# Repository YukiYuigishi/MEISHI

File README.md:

# MEISHI
[2022 v1.0](https://github.com/YukiYuigishi/MEISHI/tree/master/PCB/MEISHI2022)

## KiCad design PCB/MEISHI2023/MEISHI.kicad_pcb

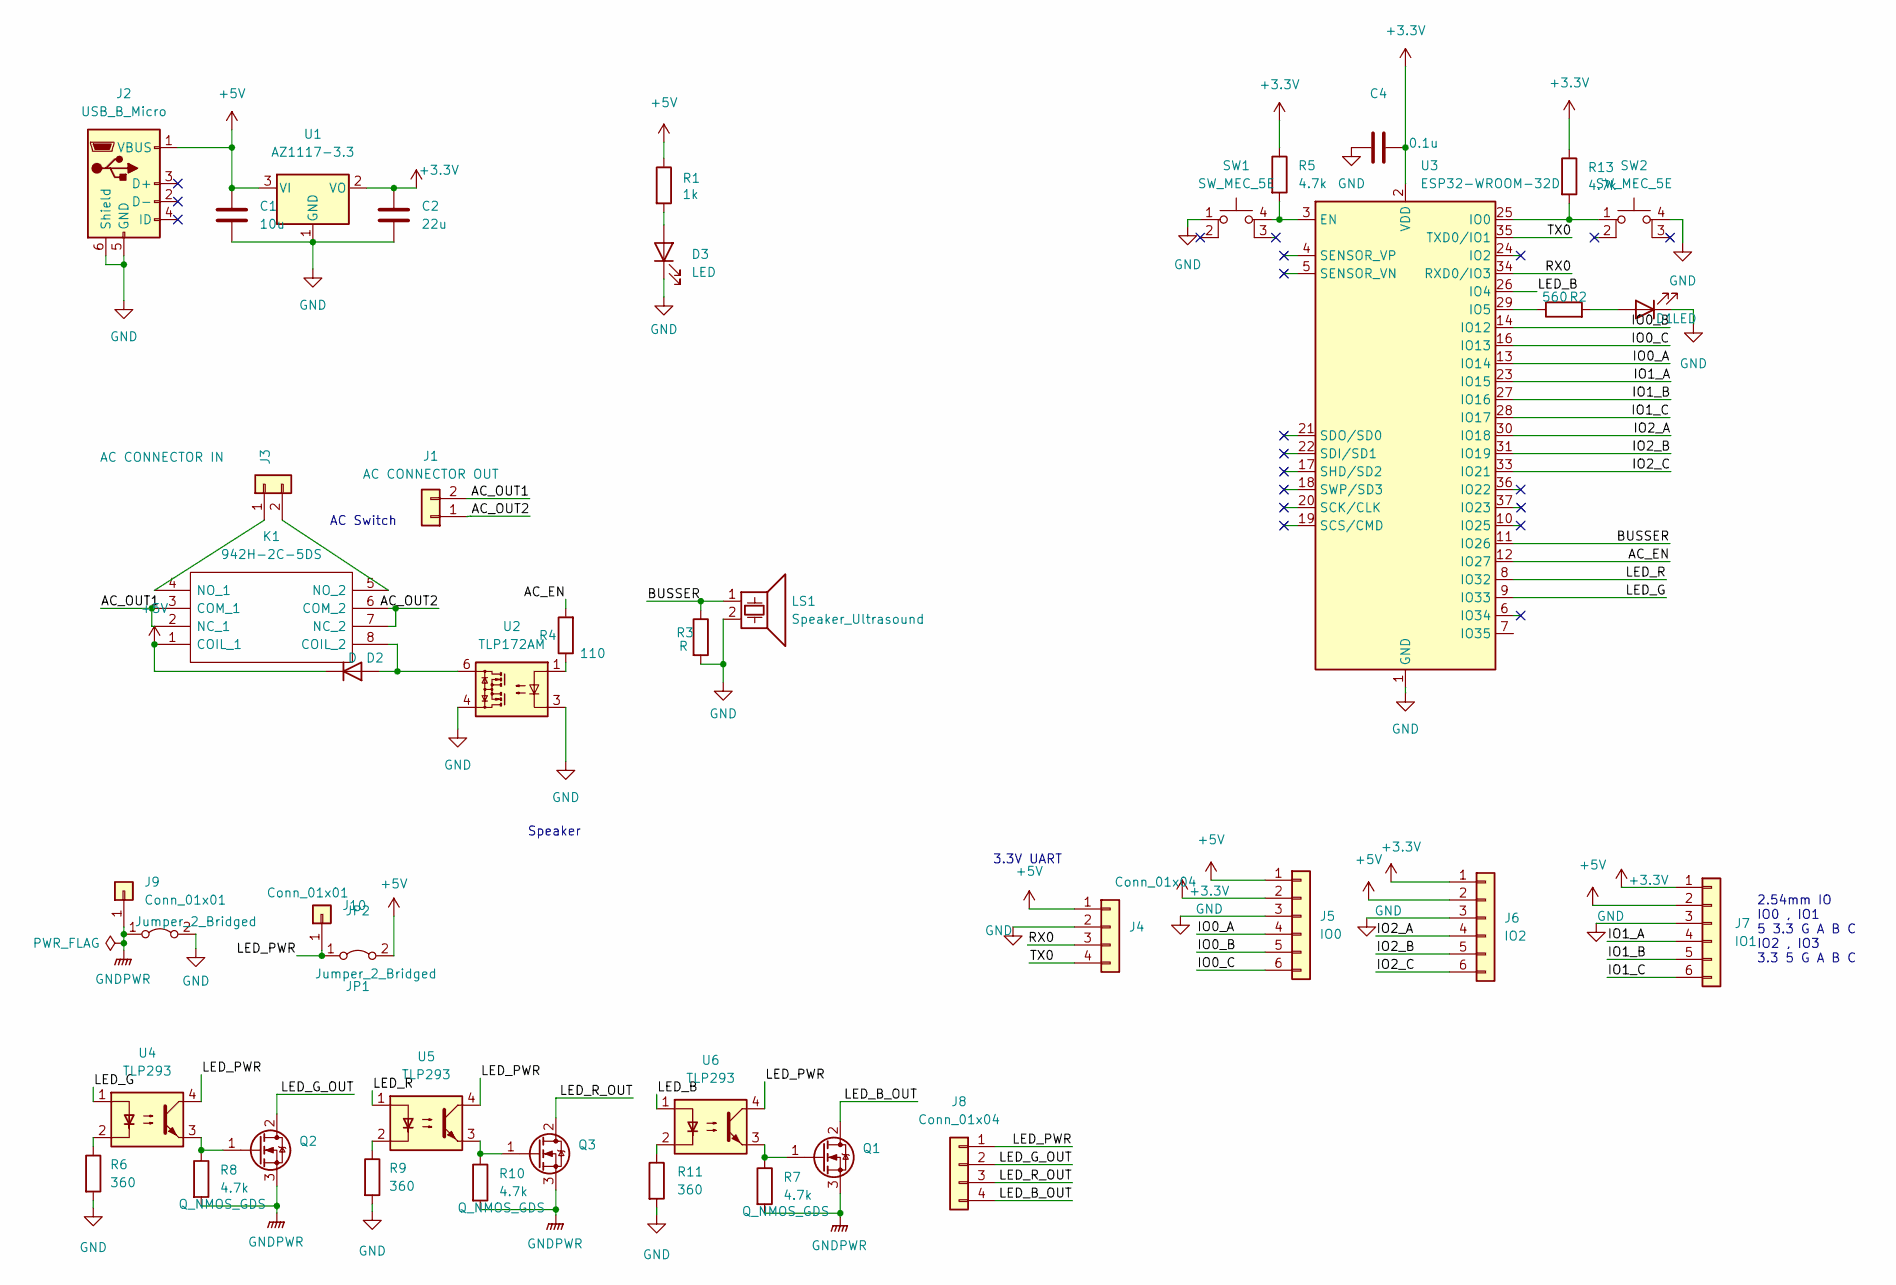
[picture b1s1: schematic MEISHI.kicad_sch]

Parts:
C1: 10u; C_0805_2012Metric_Pad1.18x1.45mm_HandSolder
C2: 22u; C_0805_2012Metric_Pad1.18x1.45mm_HandSolder
C4: 0.1u; C_0805_2012Metric_Pad1.18x1.45mm_HandSolder
D1, D3: LED; LED_0603_1608Metric_Pad1.05x0.95mm_HandSolder
D2: D; D_SOD-128
J1: AC CONNECTOR OUT; JST_VH_B2P-VH_1x02_P3.96mm_Vertical
J2: USB_B_Micro; Micro-USB-J91(Marutsu)
J3: AC CONNECTOR IN; JST_VH_B2P-VH_1x02_P3.96mm_Vertical
J4, J8: Conn_01x04; JST_XH_B4B-XH-A_1x04_P2.50mm_Vertical
J5: IO0; JST_XH_B6B-XH-A_1x06_P2.50mm_Vertical
J6: IO2; JST_XH_B6B-XH-A_1x06_P2.50mm_Vertical
J7: IO1; JST_XH_B6B-XH-A_1x06_P2.50mm_Vertical
J9, J10: Conn_01x01; SolderWirePad_1x01_SMD_5x10mm
JP1: Jumper_2_Bridged; SolderJumper-2_P1.3mm_Open_RoundedPad1.0x1.5mm
JP2: Jumper_2_Bridged; D_SOD-123F
K1: 942H-2C-5DS; 942H2C5DS; Manufacturer_Part_Number 942H-2C-5DS
LS1: Speaker_Ultrasound; Buzzer_TDK_PS1240P02BT_D12.2mm_H6.5mm
Q1, Q2, Q3: Q_NMOS_GDS; TO-252-2
R1: 1k; R_0603_1608Metric_Pad0.98x0.95mm_HandSolder
R2: 560; R_0603_1608Metric_Pad0.98x0.95mm_HandSolder
R3: R; R_0603_1608Metric_Pad0.98x0.95mm_HandSolder
R4: 110; R_0603_1608Metric_Pad0.98x0.95mm_HandSolder
R5, R7, R8, R10, R13: 4.7k; R_0603_1608Metric_Pad0.98x0.95mm_HandSolder
R6, R9, R11: 360; R_0603_1608Metric_Pad0.98x0.95mm_HandSolder
SW1, SW2: SW_MEC_5E; SKRPABE010
U1: AZ1117-3.3; SOT-223-3_TabPin2
U2: TLP172AM; MFSOP6-4_4.4x3.6mm_P1.27mm
U3: ESP32-WROOM-32D; ESP32-WROOM-32
U4, U5, U6: TLP293; SOIC-4_4.55x2.6mm_P1.27mm

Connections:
+3V3: C2.1, C4.2, J5.2, J6.1, J7.1, R5.1, R13.1, U1.2 (VO), U3.2 (VDD)
+5V: C1.1, D2.1 (K), J2.1 (VBUS), J4.1, J5.1, J6.2, J7.2, JP2.2 (B), K1.1 (COIL_1), R1.1, U1.3 (VI)
/AC_EN: R4.2, U3.12 (IO27)
/AC_OUT1: J1.2, K1.2 (NC_1), K1.3 (COM_1)
/AC_OUT2: J1.1, K1.6 (COM_2), K1.7 (NC_2)
/BUSSER: LS1.1, R3.1, U3.11 (IO26)
/IO0_A: J5.4, U3.13 (IO14)
/IO0_B: J5.5, U3.14 (IO12)
/IO0_C: J5.6, U3.16 (IO13)
/IO1_A: J7.4, U3.23 (IO15)
/IO1_B: J7.5, U3.27 (IO16)
/IO1_C: J7.6, U3.28 (IO17)
/IO2_A: J6.4, U3.30 (IO18)
/IO2_B: J6.5, U3.31 (IO19)
/IO2_C: J6.6, U3.33 (IO21)
/LED_B: U3.26 (IO4), U6.1
/LED_B_OUT: J8.4, Q1.2 (D)
/LED_G: U3.9 (IO33), U4.1
/LED_G_OUT: J8.2, Q2.2 (D)
/LED_PWR: J8.1, J10.1, JP2.1 (A), U4.4, U5.4, U6.4
/LED_R: U3.8 (IO32), U5.1
/LED_R_OUT: J8.3, Q3.2 (D)
/RX0: J4.3, U3.34 (RXD0/IO3)
/TX0: J4.4, U3.35 (TXD0/IO1)
GND: C1.2, C2.2, C4.1, D1.1 (K), D3.1 (K), J2.5 (GND), J2.6 (Shield), J4.2, J5.3, J6.3, J7.3, JP1.2 (B), LS1.2, R3.2, R6.2, R9.2, R11.2, SW1.1, SW2.4 (A), U1.1 (GND), U2.3, U2.4, U3.1 (GND), U3.15 (GND), U3.38 (GND), U3.39 (GND)
GNDPWR: J9.1, JP1.1 (A), Q1.3 (S), Q2.3 (S), Q3.3 (S), R7.2, R8.2, R10.2
unnamed: D1.2 (A), R2.2
unnamed: D2.2 (A), K1.8 (COIL_2), U2.6
unnamed: D3.2 (A), R1.2
unnamed: J3.1, K1.4 (NO_1)
unnamed: J3.2, K1.5 (NO_2)
unnamed: Q1.1 (G), R7.1, U6.3
unnamed: Q2.1 (G), R8.1, U4.3
unnamed: Q3.1 (G), R10.1, U5.3
unnamed: R2.1, U3.29 (IO5)
unnamed: R4.1, U2.1
unnamed: R5.2, SW1.4 (A), U3.3 (EN)
unnamed: R6.1, U4.2
unnamed: R9.1, U5.2
unnamed: R11.1, U6.2
unnamed: R13.2, SW2.1, U3.25 (IO0)

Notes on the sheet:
2.54mm IO IO0 , IO1 5 3.3 G A B C IO2 , IO3 3.3 5 G A B C
Speaker
AC Switch
3.3V UART

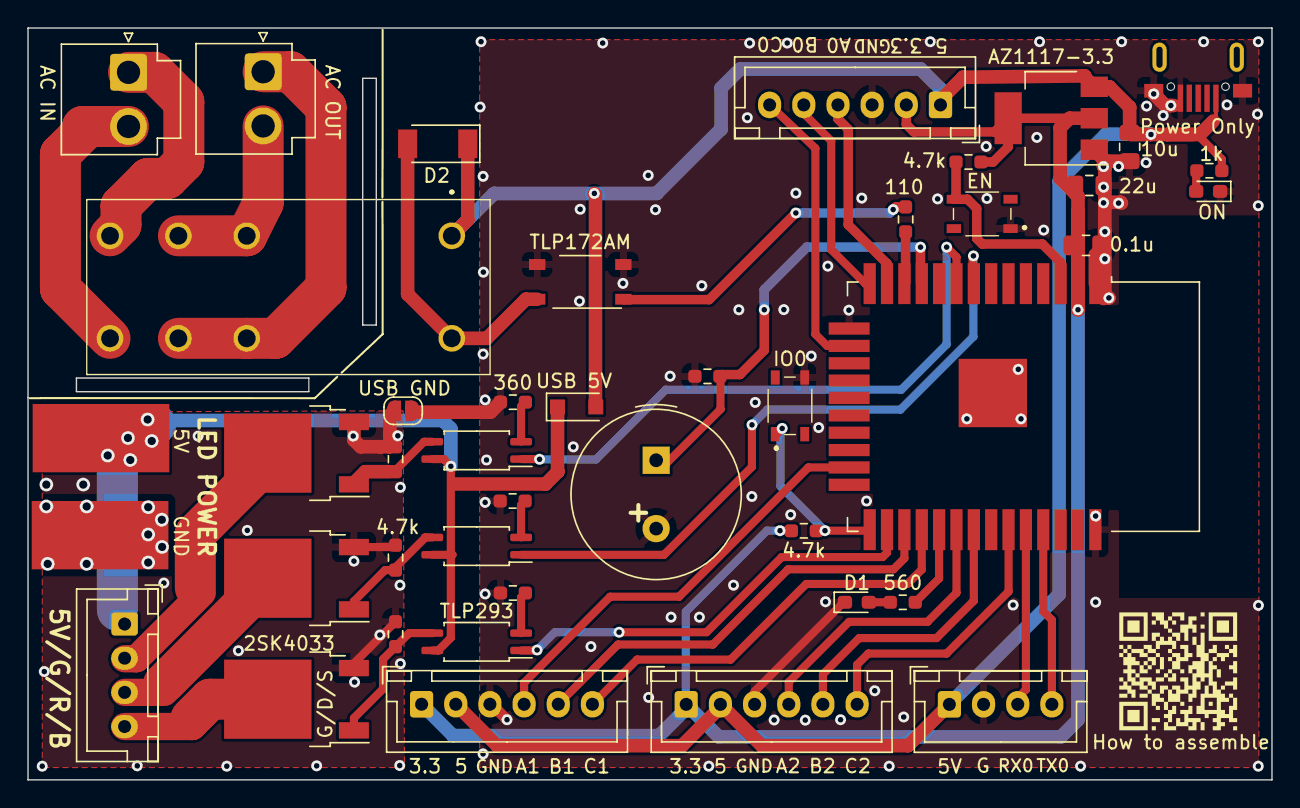
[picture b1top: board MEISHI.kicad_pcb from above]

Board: 2 copper layers, 91.0 x 55.0 mm, 43 parts (0 on the bottom side), 41 nets.

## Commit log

2022-06-02 add WIP PCB
2022-06-05 add gitignore
2022-06-05 update gitignore
2022-06-05 rm fp-info-cache
2022-06-05 rename MEISHI DIR
2022-06-05 reorder files
2022-06-05 feat MEISHI
2022-06-08 fix pcb
2022-06-25 feat headerfile
2023-08-06 feat:MEISHI2023
